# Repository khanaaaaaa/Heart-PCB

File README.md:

# Heart-PCB

A starter project through Stasis which I made a heart shaped version, was a bit intimidating at first but somehow pulled through. Also had to redo the pcb because I couldn't figure out where I went wrong previously.

Schematic:

PCB:

3D View:

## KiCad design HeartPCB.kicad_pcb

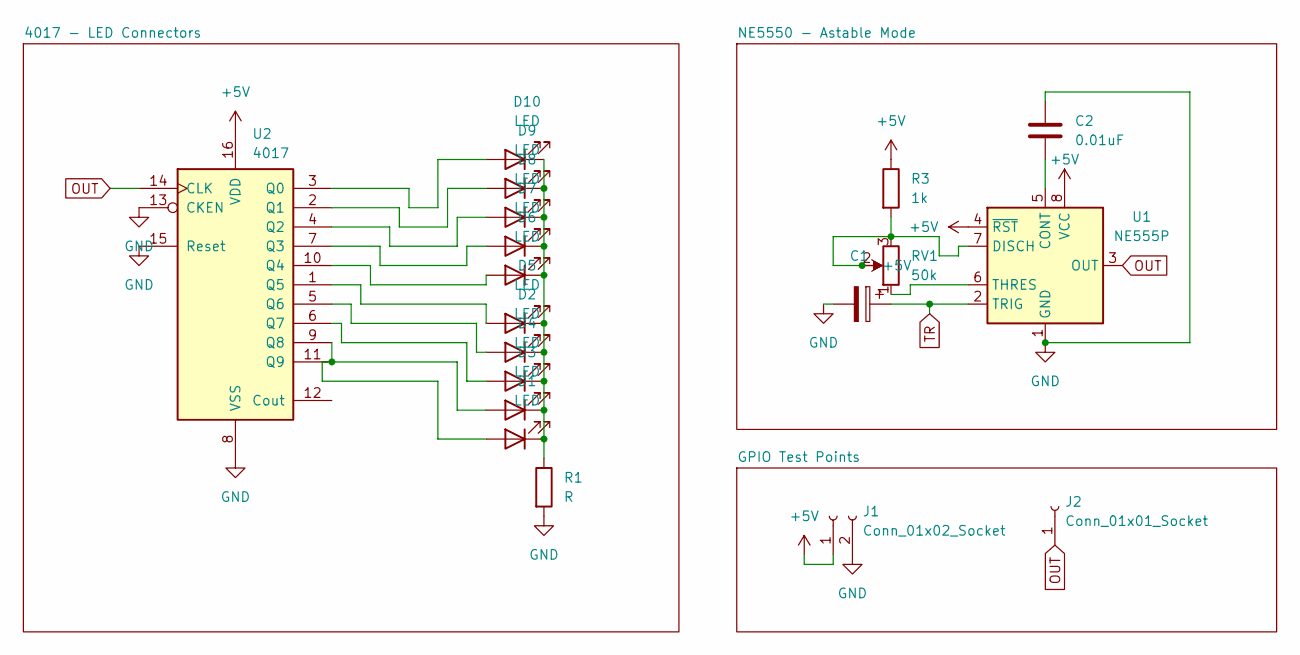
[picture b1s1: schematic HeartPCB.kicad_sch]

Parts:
C1: 1uF; CP_Radial_D5.0mm_P2.50mm
C2: 0.01uF; C_Disc_D5.0mm_W2.5mm_P5.00mm
D1, D2, D3, D4, D5, D6, D7, D8, D9, D10: LED; LED_D5.0mm
J1: Conn_01x02_Socket; PinHeader_1x02_P2.54mm_Vertical
J2: Conn_01x01_Socket; PinHeader_1x01_P2.54mm_Vertical
R1: R; R_Axial_DIN0207_L6.3mm_D2.5mm_P10.16mm_Horizontal
R3: 1k; R_Axial_DIN0207_L6.3mm_D2.5mm_P10.16mm_Horizontal
RV1: 50k; Potentiometer_Alpha_RD901F-40-00D_Single_Vertical
U1: NE555P; DIP-8_W7.62mm
U2: 4017; N16

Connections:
+5V: J1.1, R3.1, R3.2, RV1.2, RV1.3, U1.4 (~RST), U1.7 (DISCH), U1.8 (VCC), U2.16 (VDD)
GND: C1.2, C2.1, J1.2, R1.2, U1.1 (GND), U2.8 (VSS), U2.13 (CKEN), U2.15 (Reset)
unnamed: D1.2 (A), D3.2 (A), U2.9 (Q8), U2.11 (Q9)
unnamed: D1.1 (K), D2.1 (K), D3.1 (K), D4.1 (K), D5.1 (K), D6.1 (K), D7.1 (K), D8.1 (K), D9.1 (K), D10.1 (K), R1.1
unnamed: D2.2 (A), U2.5 (Q6)
unnamed: D4.2 (A), U2.6 (Q7)
unnamed: D5.2 (A), U2.1 (Q5)
unnamed: D6.2 (A), U2.10 (Q4)
unnamed: D7.2 (A), U2.7 (Q3)
unnamed: D8.2 (A), U2.4 (Q2)
unnamed: D9.2 (A), U2.2 (Q1)
unnamed: D10.2 (A), U2.3 (Q0)
unnamed: C2.2, U1.5 (CONT)
unnamed: RV1.1, U1.6 (THRES)
OUT: J2.1, U1.3 (OUT), U2.14 (CLK)
TR: C1.1, U1.2 (TRIG)

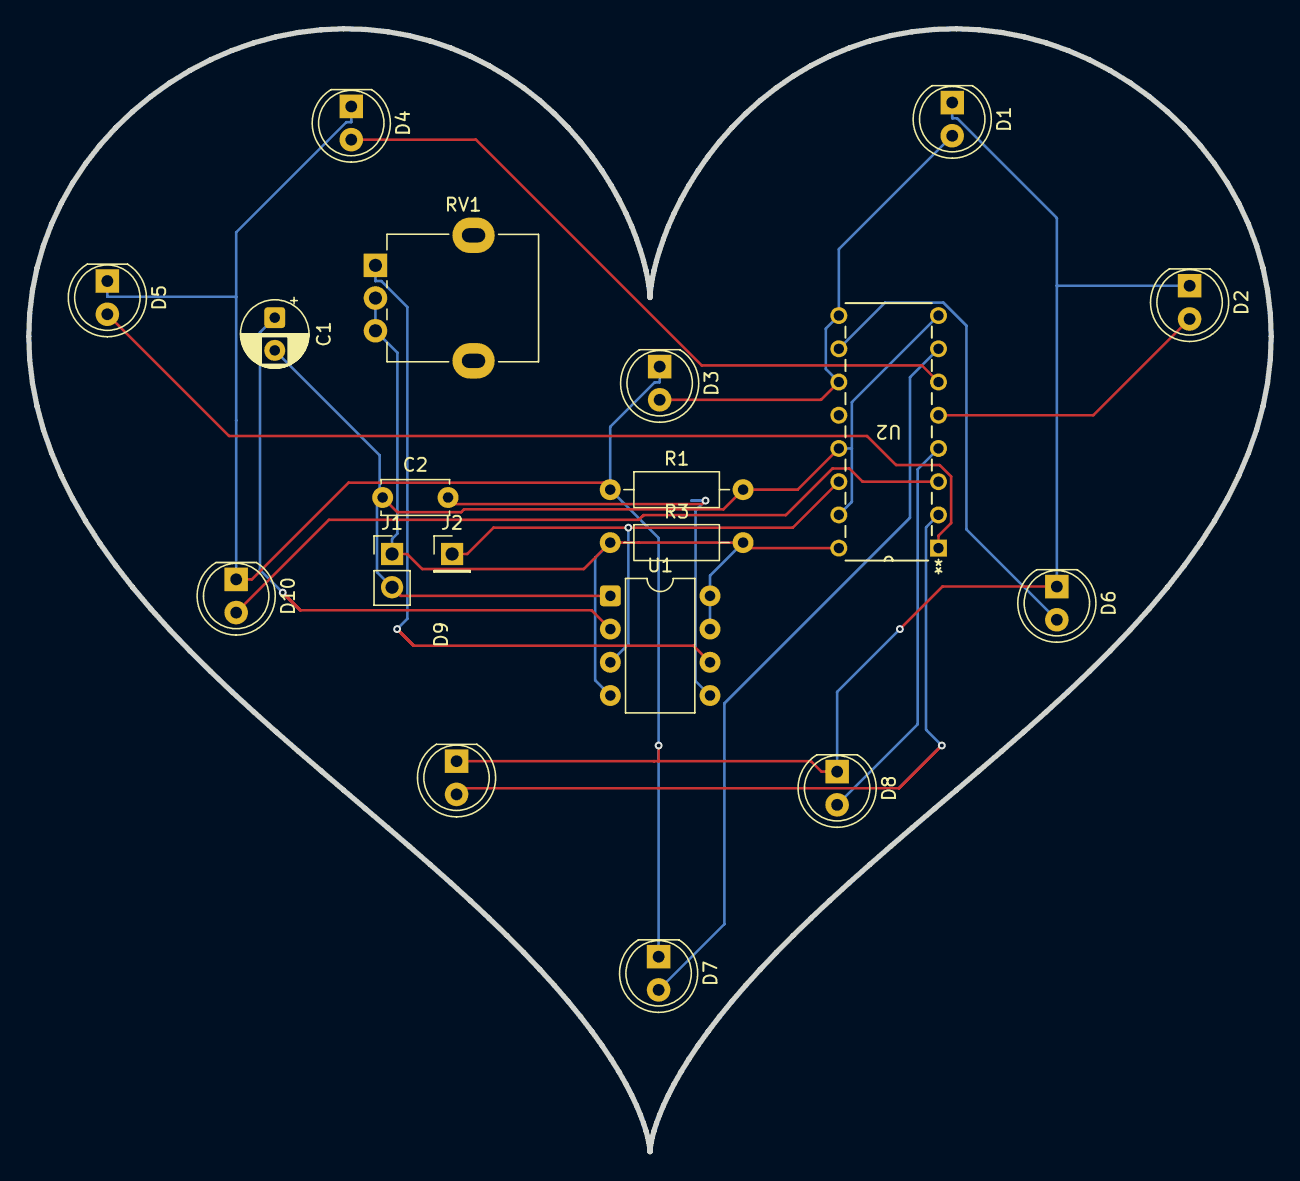
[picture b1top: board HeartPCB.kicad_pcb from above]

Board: 2 copper layers, 95.0 x 85.9 mm, 19 parts (0 on the bottom side), 16 nets.

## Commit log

2026-04-13 Add files via upload
    Redid the whole PCB because of the dimension
2026-04-13 Update README with schematic and PCB images
    Added schematic, PCB, and 3D view images to README.
2026-04-13 Update README with project details and challenges
    Added a personal project description and challenges faced.
